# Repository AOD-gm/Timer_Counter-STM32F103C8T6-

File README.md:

# TIMER COUNTER

---
### 📂 Chi tiết thư mục

<details>
<summary><b>📂 Bấm để xem cấu trúc thư mục dự án (Project Structure)</b></summary>

```text
📂 Timer Counter
├── 📦 Core
│   ├── 📂 Inc
│   │   ├── 📜 DS1307.h        # Thư viện RTC DS3231/DS1307
│   │   ├── 📜 Esp_01.h        # Thư viện giao tiếp ESP-01
│   │   ├── 📜 FontSSD1306.h   # Font chữ cho OLED SSD1306
│   │   ├── 📜 HLK_LD2410.h    # Driver cảm biến Radar hiện diện
│   │   ├── 📜 Keypad.h        # Thư viện ma trận phím
│   │   ├── 📜 Menu_UI.h       # Logic Menu & Giao diện OLED
│   │   ├── 📜 MH-R38.h        # Giải mã tín hiệu Remote IR
│   │   └── 📜 SSD1306.h       # Thư viện điều khiển màn hình OLED
│   └── 📂 Src
│       ├── 📜 main.c          # Luồng xử lý chính
│       ├── 📜 Menu_UI.c       # Cấu trúc hiển thị Menu
│       └── 📜 ...             # Các file xử lý tương ứng (.c)
├── 📦 Esp-01
│   ├── 📂 inc
│   │   └── 📜 wifiConfig.h    # Cấu hình WiFi & Web Server
│   └── 📂 src
│       └── 📜 WifiConfig.cpp  # Xử lý logic kết nối
└── 📦 PCB
    ├── 📂 GiaCong             # File Gerber, BOM để đặt mạch
    └── 📂 Timer_Counter       # File thiết kế gốc (KiCad)
 ```
 </details>

### 🛠️ Phần cứng sử dụng

**1. Vi điều khiển trung tâm**
* STM32F103C8T6 (ARM Cortex-M3)

**2. Cảm biến & Module ngoại vi**
* **Mô-đun kết nối:** ESP8266 (ESP-01) cấu hình Web Server.
* **Cảm biến hiện diện:** Radar HLK-LD2410C (nhận diện vi chuyển động).
* **Module thời gian thực:** DS3231 / DS1307 (lưu giữ ngày giờ).
* **Màn hình hiển thị:** OLED 0.96 inch (IC SSD1306).

* **Khối điều khiển & Giao tiếp:** Bàn phím ma trận (Keypad) & MH-R38 (nhận tín hiệu Remote IR)

## Sơ đồ nối chân 
| 🛠️ Phần cứng | 📌 Chân STM32 | 🔗 Giao tiếp | 📝 Chức năng |
| :--- | :---: | :---: | :--- |
| 🖥️ **OLED SSD1306** | `PB6 (SCL)`<br>`PB7 (SDA)` | `I2C1` | Hiển thị thông tin giao diện người dùng |
| 🌐 **ESP-01 (WiFi)** | `PA9 (TX)`<br>`PA10 (RX)` | `UART1` | Web Server & Phát WiFi điều khiển từ xa |
| ⏳ **RTC DS3231** | `PB6 (SCL)`<br>`PB7 (SDA)` | `I2C1` | Lưu thời gian & Báo thức (chạy khi mất điện) |
| 📡 **Radar LD2410** | `PA2 (TX)`<br>`PA3 (RX)` | `UART2` | Nhận diện người (vi chuyển động) |
| 🎛️ **Keypad 4x4** | `PB12-15`<br>`PA4-7` | `GPIO` | Điều khiển Menu |
| 🖲️ **Mắt thu IR** | `PA1` | `TIM2` | Nhận tín hiệu Remote hồng ngoại

## Yêu Cầu
<p align="center">

  <br/><br/>

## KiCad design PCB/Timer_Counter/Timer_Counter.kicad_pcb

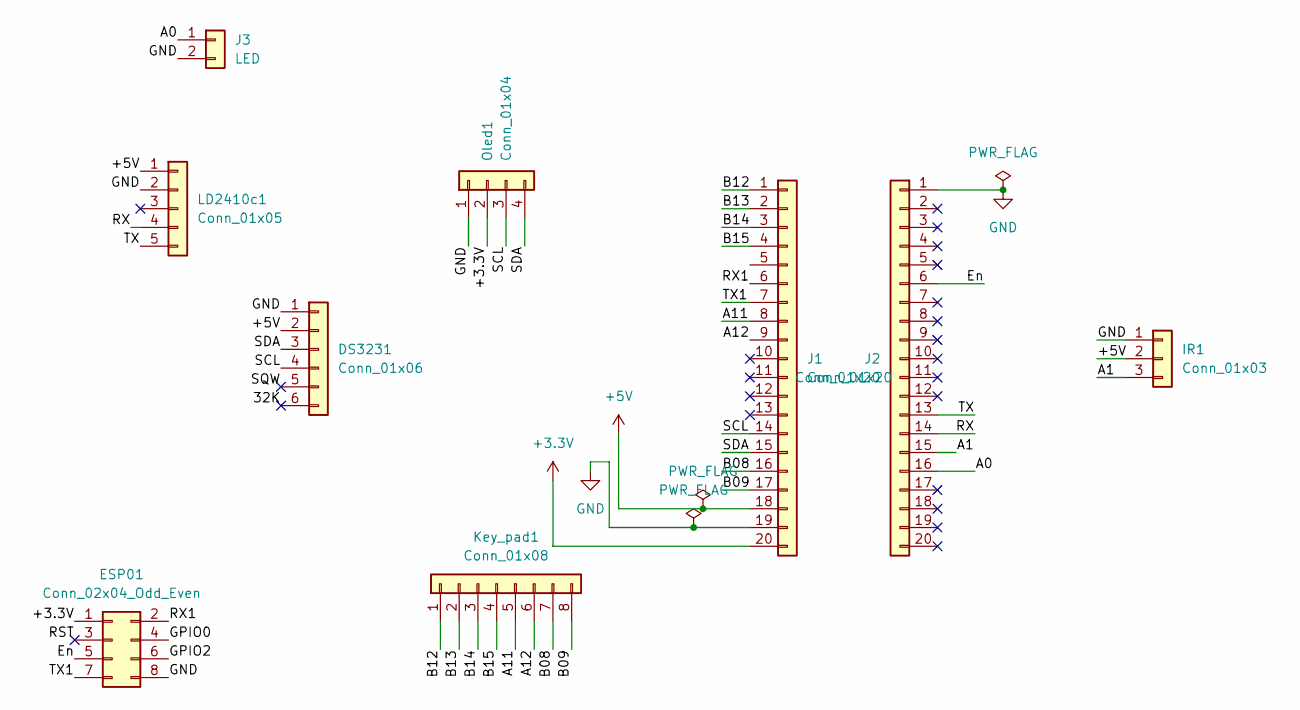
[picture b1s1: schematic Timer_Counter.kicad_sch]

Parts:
DS3231: Conn_01x06; PinSocket_1x06_P2.54mm_Vertical
ESP01: Conn_02x04_Odd_Even; PinSocket_2x04_P2.54mm_Vertical
IR1: Conn_01x03; PinSocket_1x03_P2.54mm_Vertical
J1, J2: Conn_01x20; PinSocket_1x20_P2.54mm_Vertical
J3: LED; PinSocket_1x02_P2.00mm_Vertical
Key_pad1: Conn_01x08; PinHeader_1x08_P2.54mm_Vertical
LD2410c1: Conn_01x05; PinSocket_1x05_P2.54mm_Horizontal
Oled1: Conn_01x04; PinSocket_1x04_P2.54mm_Horizontal

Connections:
+3.3V: ESP01.1, J1.20, Oled1.2
+5V: DS3231.2, IR1.2, J1.18, LD2410c1.1
/32K: DS3231.6
/A0: J2.16, J3.1
/A1: IR1.3, J2.15
/A11: J1.8, Key_pad1.5
/A12: J1.9, Key_pad1.6
/B08: J1.16, Key_pad1.7
/B09: J1.17, Key_pad1.8
/B12: J1.1, Key_pad1.1
/B13: J1.2, Key_pad1.2
/B14: J1.3, Key_pad1.3
/B15: J1.4, Key_pad1.4
/En: ESP01.5, J2.6
/GPIO0: ESP01.4
/GPIO2: ESP01.6
/RST: ESP01.3
/RX: J2.14, LD2410c1.4
/RX1: ESP01.2, J1.6
/SCL: DS3231.4, J1.14, Oled1.3
/SDA: DS3231.3, J1.15, Oled1.4
/SQW: DS3231.5
/TX: J2.13, LD2410c1.5
/TX1: ESP01.7, J1.7
GND: DS3231.1, ESP01.8, IR1.1, J1.19, J2.1, J3.2, LD2410c1.2, Oled1.1

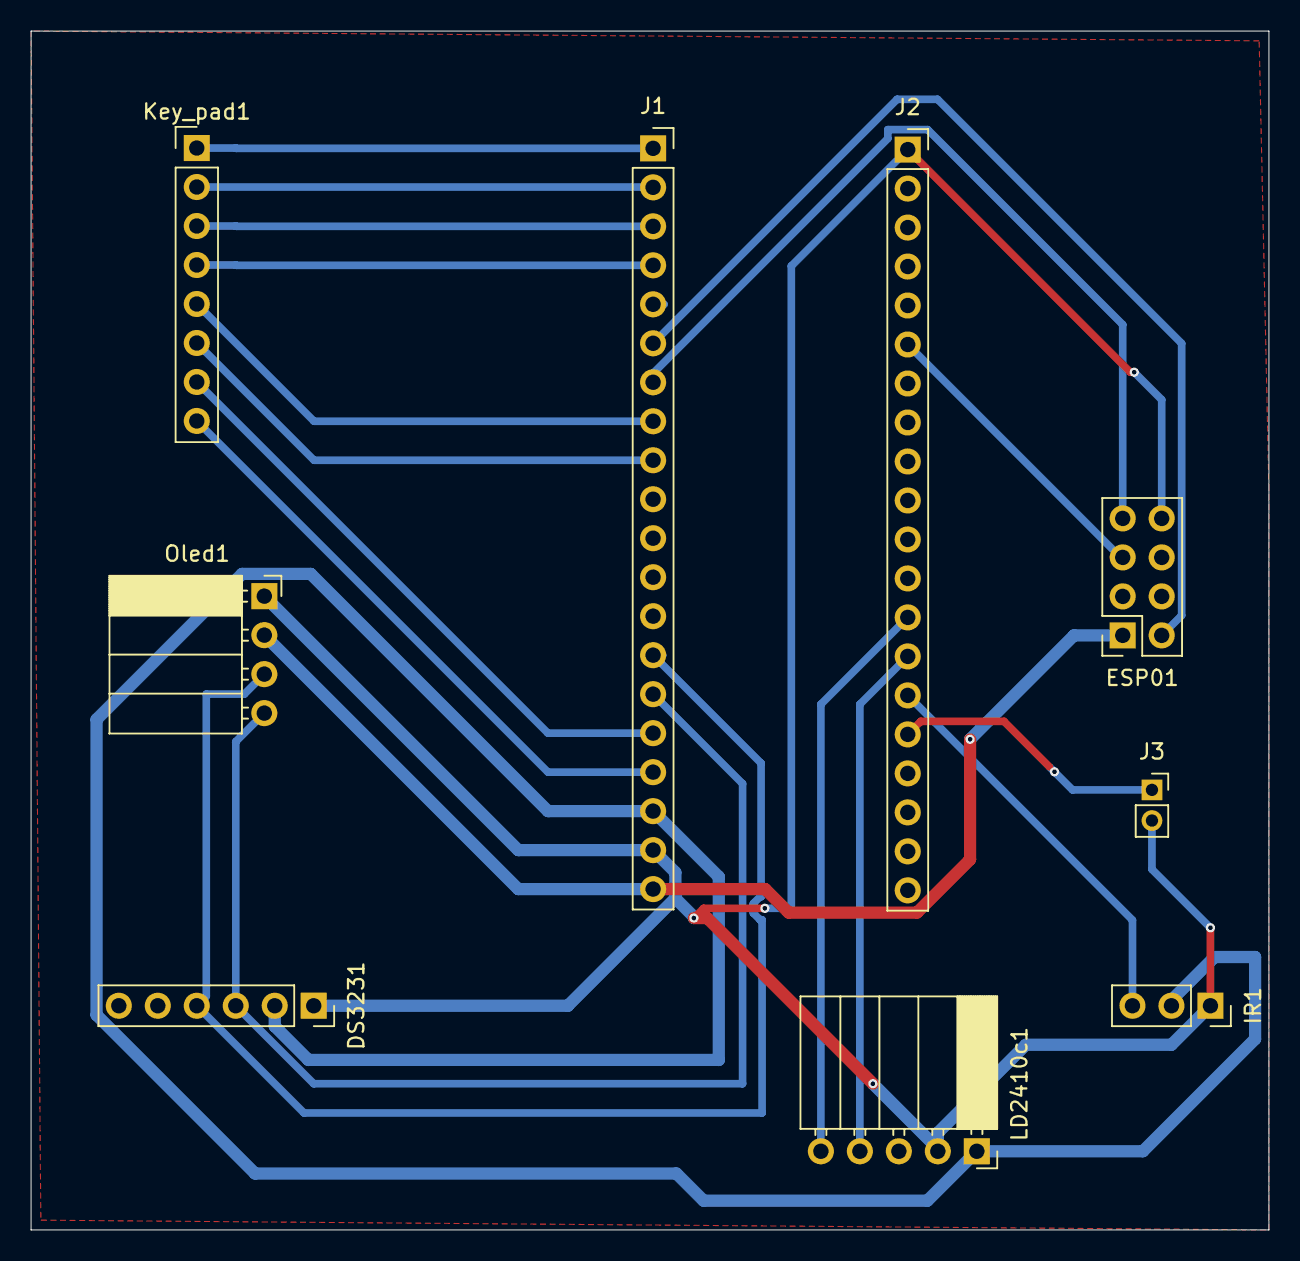
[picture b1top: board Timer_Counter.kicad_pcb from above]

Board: 2 copper layers, 80.6 x 78.1 mm, 9 parts (0 on the bottom side), 20 nets.

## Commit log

2026-03-22 First code
2026-04-26 Xong hen gio bat tat led va ma hinh tren oled
2026-04-27 Tach file de nhin va them thu vien IR
2026-04-28 Thêm font 11x18 vào ssd1306
2026-04-28 chinh sua file rac, them Menu_UI de quan ly oled va them kich thuoc 11x18 oled
2026-04-29 Add hello file with initial content
2026-05-01 thêm thư viện HLK_LD2410C
2026-05-01 Thêm file pcb
2026-05-01 Thêm vài chức năng SSD1306
2026-05-02 Chinh sua Oled Logic
2026-05-02 test thu
2026-05-02 Create esp01
2026-05-02 Update esp01
2026-05-03 Sua loi logic menu
2026-05-03 Them pcb mơi sửa vào
2026-05-04 Them System Proccess để xử lý thiết bị ngoài
2026-05-08 Sửa lại vài thứ
2026-05-08 Hoàn thành logic code
2026-05-09 Xong mọi thứ
2026-05-09 Cập nhật file PCB
2026-05-09 Sửa IR
2026-05-09 Add project title to README
2026-05-09 Make project title bold in README
2026-05-09 Fix formatting of project title in README
2026-05-09 Fix formatting in README.md for Timer_Counter section
2026-05-09 Update README.md with project structure changes
    Removed unnecessary lines and updated project structure.
2026-05-16 Cap nhat file thiet ke PCB
2026-05-19 Fix alarm and radar logic for ESP01
2026-05-19 Da fix xong loi bao thuc ESP01 va LED
2026-05-19 siêu cấp ĩ bug alarm :(((
2026-05-19 fix vài lỗi
2026-05-30 Fix year register on ds3231 but not successful :((
2026-05-30 fix year register on DS3231 but not sucess :((
2026-05-30 seperate and add sth relate with web make it's convinience
2026-05-30 add function to set date
2026-05-30 add mode on web to easy ajust(saving mode can cause a problem because it unable esp01 so you can not remote after this
2026-05-31 fix file read
2026-05-31 level up web
2026-05-31 rm file .azure
